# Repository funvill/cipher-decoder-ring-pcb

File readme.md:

# Cipher Decoder Ring PCB

The Cipher Decoder Ring is a toy (not designed for professional use) that allows users to encrypt/decrypt messages using a rotary encoder and LED-guided interface (No screen, or computer required). This toy uses a modern [streaming encryption algorithm](https://en.wikipedia.org/wiki/Stream_cipher) [ChaCha20](https://en.wikipedia.org/wiki/Salsa20#ChaCha_variant) ([RFC7539](https://datatracker.ietf.org/doc/html/rfc7539)) that as of the year 2025 is considered strong encryption (OverKill). A 3D printed dial is fitted over the rotary encoder shaft to mimic a combination lock.

As a backup, when the [RP2040](https://www.raspberrypi.com/products/rp2040/) is connected via USB to a PC, it enumerates as a serial terminal (115200 Baud 8-N-1). A user then could send encoded or decoded messages directly to the serial terminal instead of entering them using the rotary encoder.

Created by: [Steven Smethurst](https://blog.abluestar.com/about) (@funvill)

**!!! Design has not been tested, Sent to manufacturing on 2024-Feb-27 !!!**

## Key Features

- **Stateless Encryption** – No stored keys, no stored state. If this device is captured it can't be used to decode existing encrypted messages.
- **User-Defined Seed & Nonce** – Entered via the rotary encoder for ChaCha20 encryption.
- **Multiple Encryption Modes** – Select from ChaCha20, AES-GCM, ROT13, and more.
- **USB-C Interface** – No battery, and serial interface for encoding binary data.

## How it works

### Step 1 - Select "Encrypt" or "Decrypt"

When the device is powered on

The "Encrypt" LED starts to blink. The user can rotate the dial left or right to switch between "Encrypt" or "Decrypt" mode. When the user has selected the option that they want, they push the dial to confirm their selection.

### Step 2 - Enter seed phase

The "Mode" LED turns red. This indicates that the user can enter a seed phase using the dial. Single click on the dial selects the letter used in the seed phase. A long press on the dial confirms the seed phase is and moves on to the next phase.

### Step 3 - Enter messages

The "Mode" LED turns green. The user can enter the message using the dial one letter at a time. After each letter has been entered the corresponding encoded letter will turn blue. The user writes down the blue letters to encode or decode the message.

## Project Goals

The goal of this project was to learn about [Streaming Cipher](https://en.wikipedia.org/wiki/Stream_cipher) such as [ChaCha20](https://en.wikipedia.org/wiki/Salsa20#ChaCha_variant) as well as making a toy or giveaway for conventions like Hackaday's [SuperCon](https://hackaday.io/superconference/), and Supplyframe's [Teardown](https://www.crowdsupply.com/teardown/).

A secondary goal is to be able to manufacture this board for less then $10 CAD using [JLCPCB](https://jlcpcb.com/) (No manual soldering)

## Technical Specifications

- [Seeed Studio XIAO RP2040](https://wiki.seeedstudio.com/XIAO-RP2040/) microprocessor with USB-C
- [XL-1615RGBC-WS2812B](https://jlcpcb.com/partdetail/XINGLIGHT-XL_1615RGBCWS2812B/C5349954) Individually addressable LEDs
- [EC11E09244BS](https://tech.alpsalpine.com/e/products/detail/EC11E09244BS/) Rotary Encoder

## Tools used

- [KiCad v9.0](https://www.kicad.org/) - EDA
- [EasyEDA2Kicad](https://github.com/uPesy/easyeda2kicad.py) - Converts JLCPCB parts to KiCad files.
- [Gingerbread](https://gingerbread.wntr.dev/index.html) - Converts SVG or Affinity Designer files to KiCad files.

## Preview

### Front

### Back

### Schematic

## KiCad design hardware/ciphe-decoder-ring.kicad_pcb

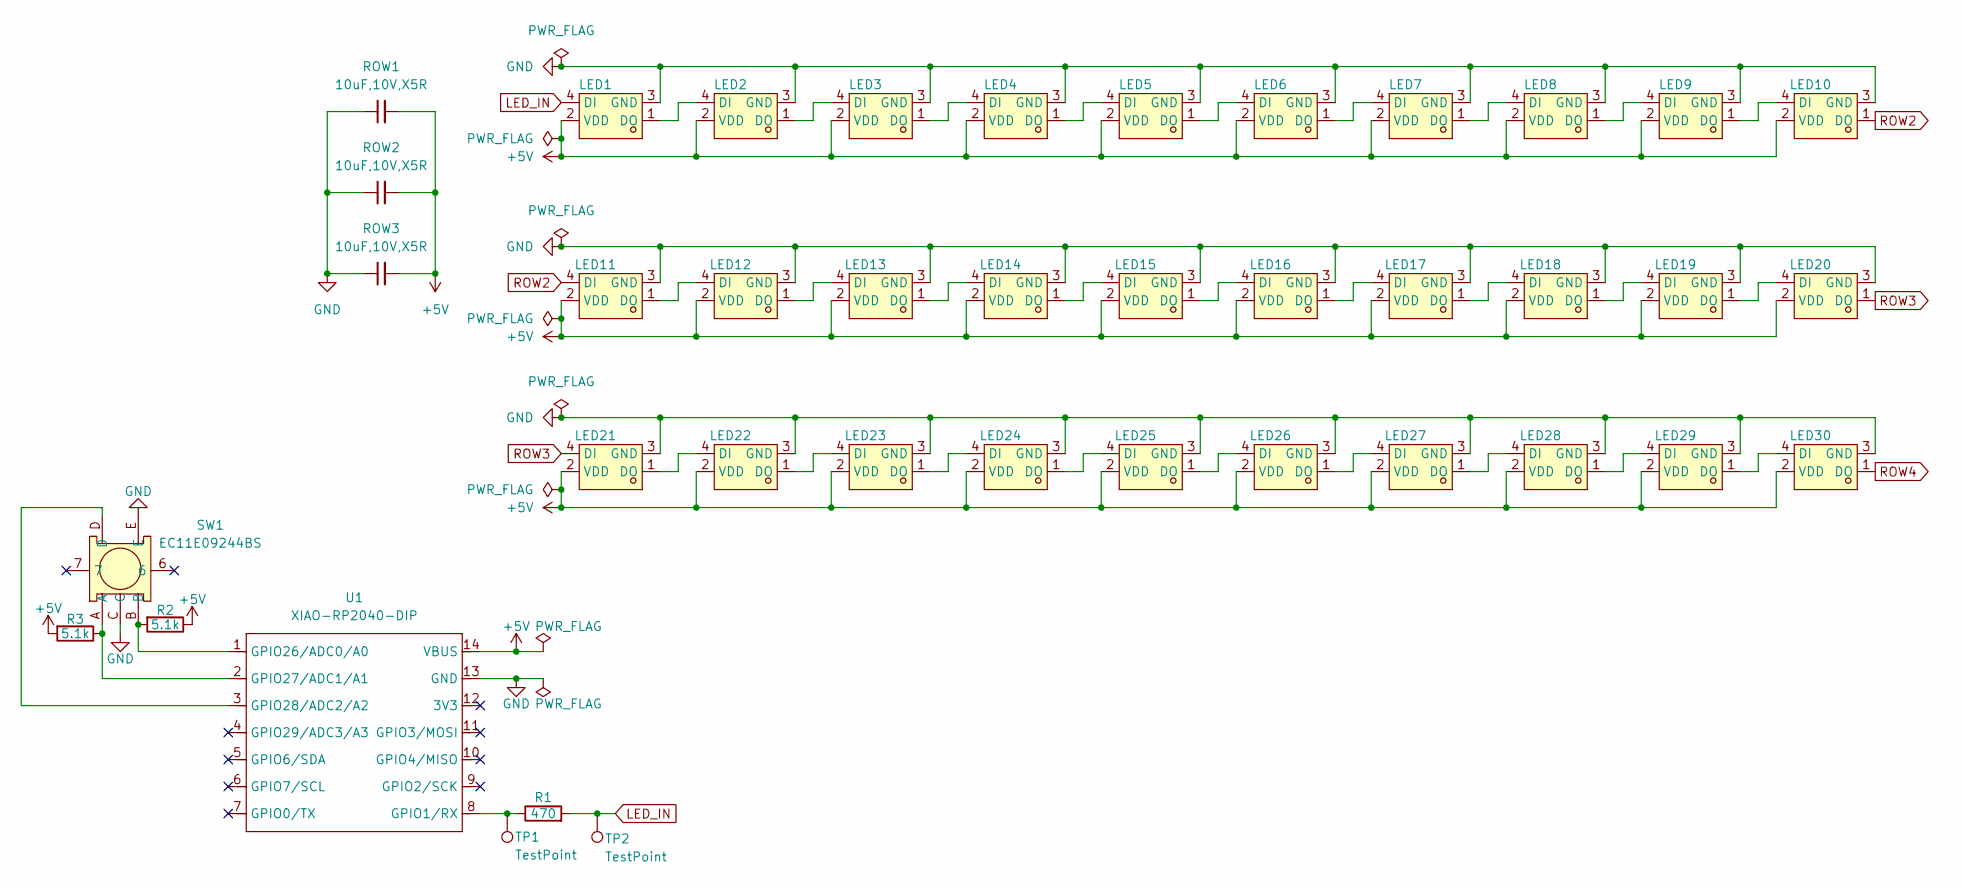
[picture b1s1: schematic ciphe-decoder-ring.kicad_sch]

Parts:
LED1, LED2, LED3, LED4, LED5, LED6, LED7, LED8, LED9, LED10, LED11, LED12, LED13, LED14, LED15, LED16, LED17, LED18, LED19, LED20, LED21, LED22, LED23, LED24, LED25, LED26, LED27, LED28, LED29, LED30: XL-1615RGBC-WS2812B; LED-SMD_4P-L1.6-W1.5_XL-1615RGBC-WS2812B; LCSC Part C5349954
R1: 470; R_0402_1005Metric; LCSC Part C25117
R2, R3: 5.1k; R_0402_1005Metric; LCSC Part C25905
ROW1, ROW2, ROW3: 10uF,10V,X5R; C_0402_1005Metric; MFGPN CL05A105KA5NQNC; LCSC C52923
SW1: EC11E09244BS; SW-TH_EC11XXXXXXXX; LCSC Part C470742
TP1, TP2: TestPoint; TestPoint_Pad_D1.5mm
U1: XIAO-RP2040-DIP; XIAO-RP2040-SMD

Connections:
+5V: LED1.2 (VDD), LED2.2 (VDD), LED3.2 (VDD), LED4.2 (VDD), LED5.2 (VDD), LED6.2 (VDD), LED7.2 (VDD), LED8.2 (VDD), LED9.2 (VDD), LED10.2 (VDD), LED11.2 (VDD), LED12.2 (VDD), LED13.2 (VDD), LED14.2 (VDD), LED15.2 (VDD), LED16.2 (VDD), LED17.2 (VDD), LED18.2 (VDD), LED19.2 (VDD), LED20.2 (VDD), LED21.2 (VDD), LED22.2 (VDD), LED23.2 (VDD), LED24.2 (VDD), LED25.2 (VDD), LED26.2 (VDD), LED27.2 (VDD), LED28.2 (VDD), LED29.2 (VDD), LED30.2 (VDD), R2.1, R3.2, ROW1.1, ROW2.1, ROW3.1, U1.14 (VBUS)
GND: LED1.3 (GND), LED2.3 (GND), LED3.3 (GND), LED4.3 (GND), LED5.3 (GND), LED6.3 (GND), LED7.3 (GND), LED8.3 (GND), LED9.3 (GND), LED10.3 (GND), LED11.3 (GND), LED12.3 (GND), LED13.3 (GND), LED14.3 (GND), LED15.3 (GND), LED16.3 (GND), LED17.3 (GND), LED18.3 (GND), LED19.3 (GND), LED20.3 (GND), LED21.3 (GND), LED22.3 (GND), LED23.3 (GND), LED24.3 (GND), LED25.3 (GND), LED26.3 (GND), LED27.3 (GND), LED28.3 (GND), LED29.3 (GND), LED30.3 (GND), ROW1.2, ROW2.2, ROW3.2, SW1.C, SW1.E, U1.13 (GND)
LED_IN: LED1.4 (DI), R1.2, TP2.1
unnamed: LED1.1 (DO), LED2.4 (DI)
unnamed: LED2.1 (DO), LED3.4 (DI)
unnamed: LED3.1 (DO), LED4.4 (DI)
unnamed: LED4.1 (DO), LED5.4 (DI)
unnamed: LED5.1 (DO), LED6.4 (DI)
unnamed: LED6.1 (DO), LED7.4 (DI)
unnamed: LED7.1 (DO), LED8.4 (DI)
unnamed: LED8.1 (DO), LED9.4 (DI)
unnamed: LED9.1 (DO), LED10.4 (DI)
unnamed: LED11.1 (DO), LED12.4 (DI)
unnamed: LED12.1 (DO), LED13.4 (DI)
unnamed: LED13.1 (DO), LED14.4 (DI)
unnamed: LED14.1 (DO), LED15.4 (DI)
unnamed: LED15.1 (DO), LED16.4 (DI)
unnamed: LED16.1 (DO), LED17.4 (DI)
unnamed: LED17.1 (DO), LED18.4 (DI)
unnamed: LED18.1 (DO), LED19.4 (DI)
unnamed: LED19.1 (DO), LED20.4 (DI)
unnamed: LED21.1 (DO), LED22.4 (DI)
unnamed: LED22.1 (DO), LED23.4 (DI)
unnamed: LED23.1 (DO), LED24.4 (DI)
unnamed: LED24.1 (DO), LED25.4 (DI)
unnamed: LED25.1 (DO), LED26.4 (DI)
unnamed: LED26.1 (DO), LED27.4 (DI)
unnamed: LED27.1 (DO), LED28.4 (DI)
unnamed: LED28.1 (DO), LED29.4 (DI)
unnamed: LED29.1 (DO), LED30.4 (DI)
unnamed: R1.1, TP1.1, U1.8 (GPIO1/RX)
unnamed: R2.2, SW1.B, U1.1 (GPIO26/ADC0/A0)
unnamed: R3.1, SW1.A, U1.2 (GPIO27/ADC1/A1)
unnamed: SW1.D, U1.3 (GPIO28/ADC2/A2)
ROW2: LED10.1 (DO), LED11.4 (DI)
ROW3: LED20.1 (DO), LED21.4 (DI)
ROW4: LED30.1 (DO)

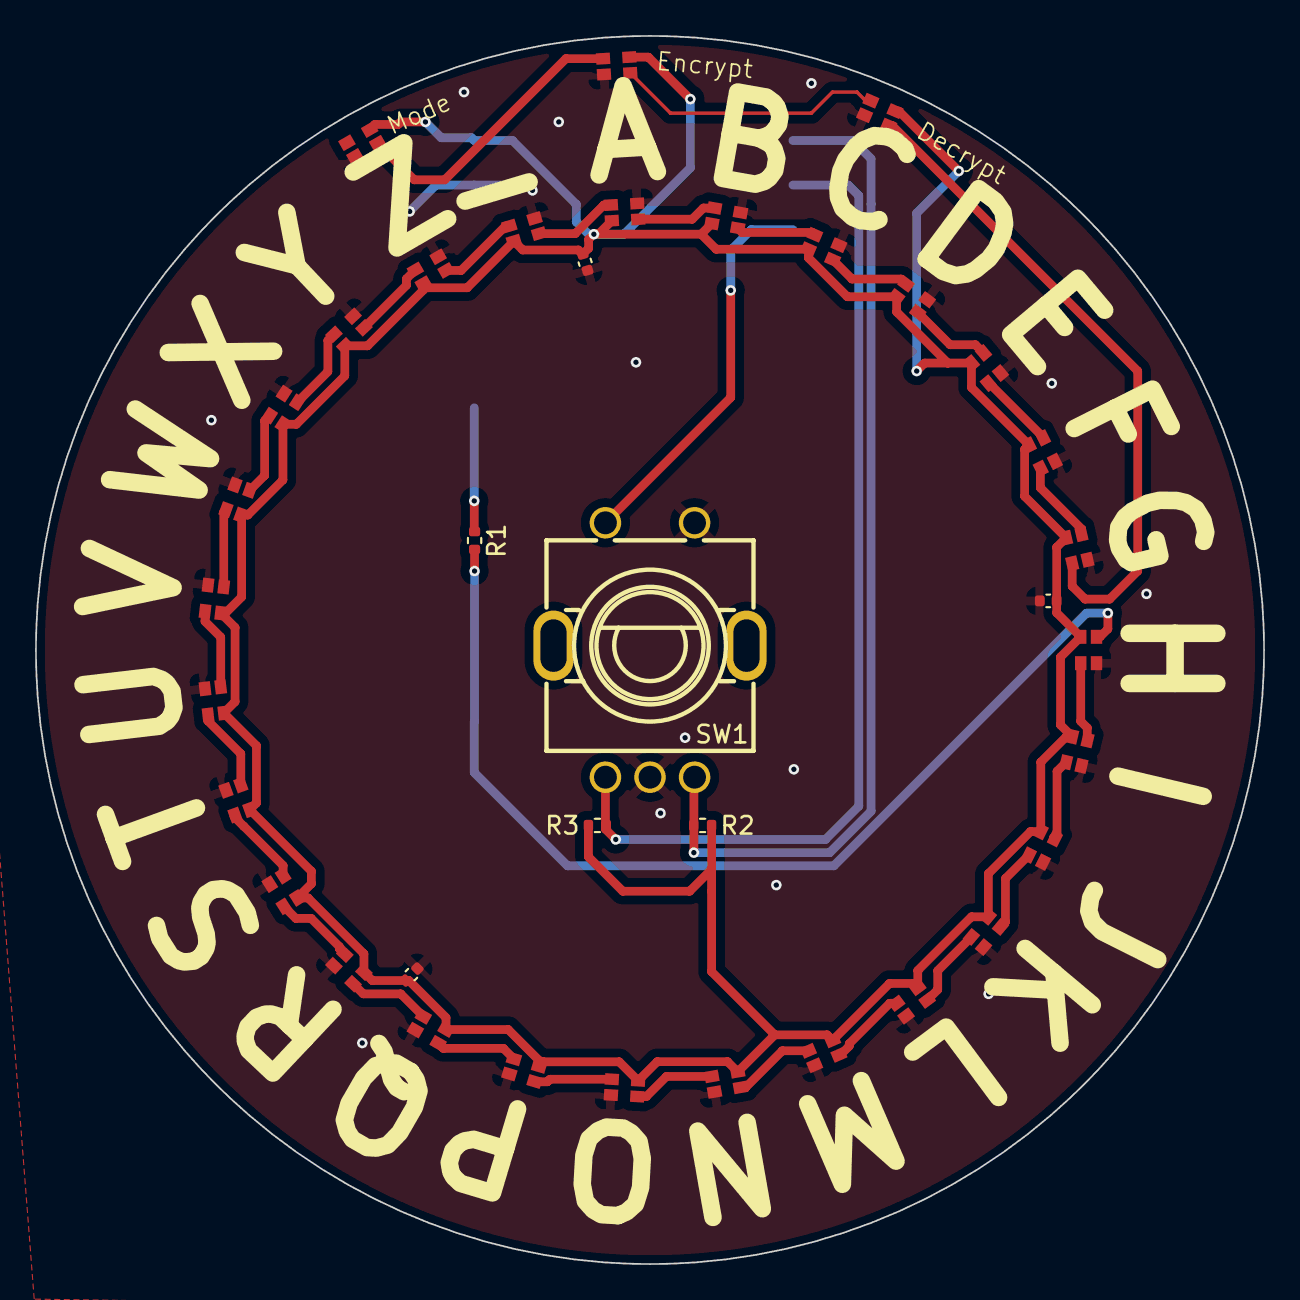
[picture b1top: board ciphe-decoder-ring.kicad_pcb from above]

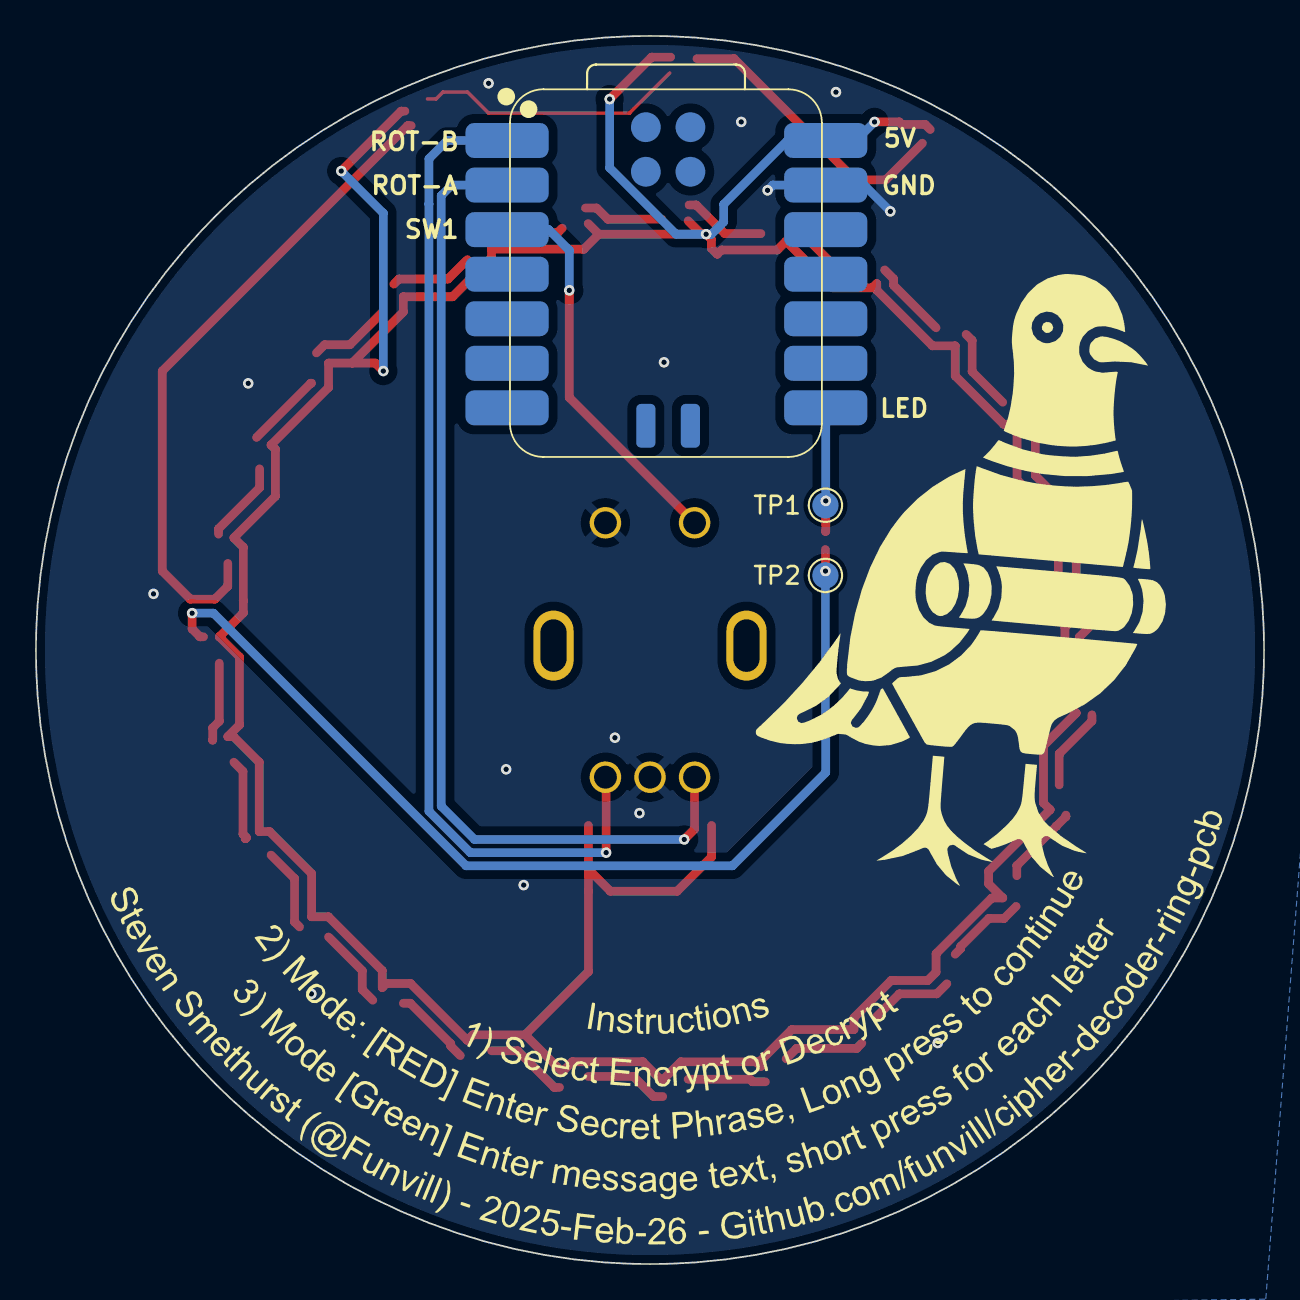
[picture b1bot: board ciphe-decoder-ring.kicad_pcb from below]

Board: 2 copper layers, 70.0 x 70.0 mm, 40 parts (3 on the bottom side), 36 nets.

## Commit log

2025-02-27 All wired up
2025-02-27 Added preview and instructions
2025-02-27 Updated readme with more information
2025-02-28 Rotated the letters, Added 3D models to 3D viewer
2025-02-28 As manufacured with JLCPCB on 2025-Feb-27
2025-02-28 Adding schematic as a PDF for review
